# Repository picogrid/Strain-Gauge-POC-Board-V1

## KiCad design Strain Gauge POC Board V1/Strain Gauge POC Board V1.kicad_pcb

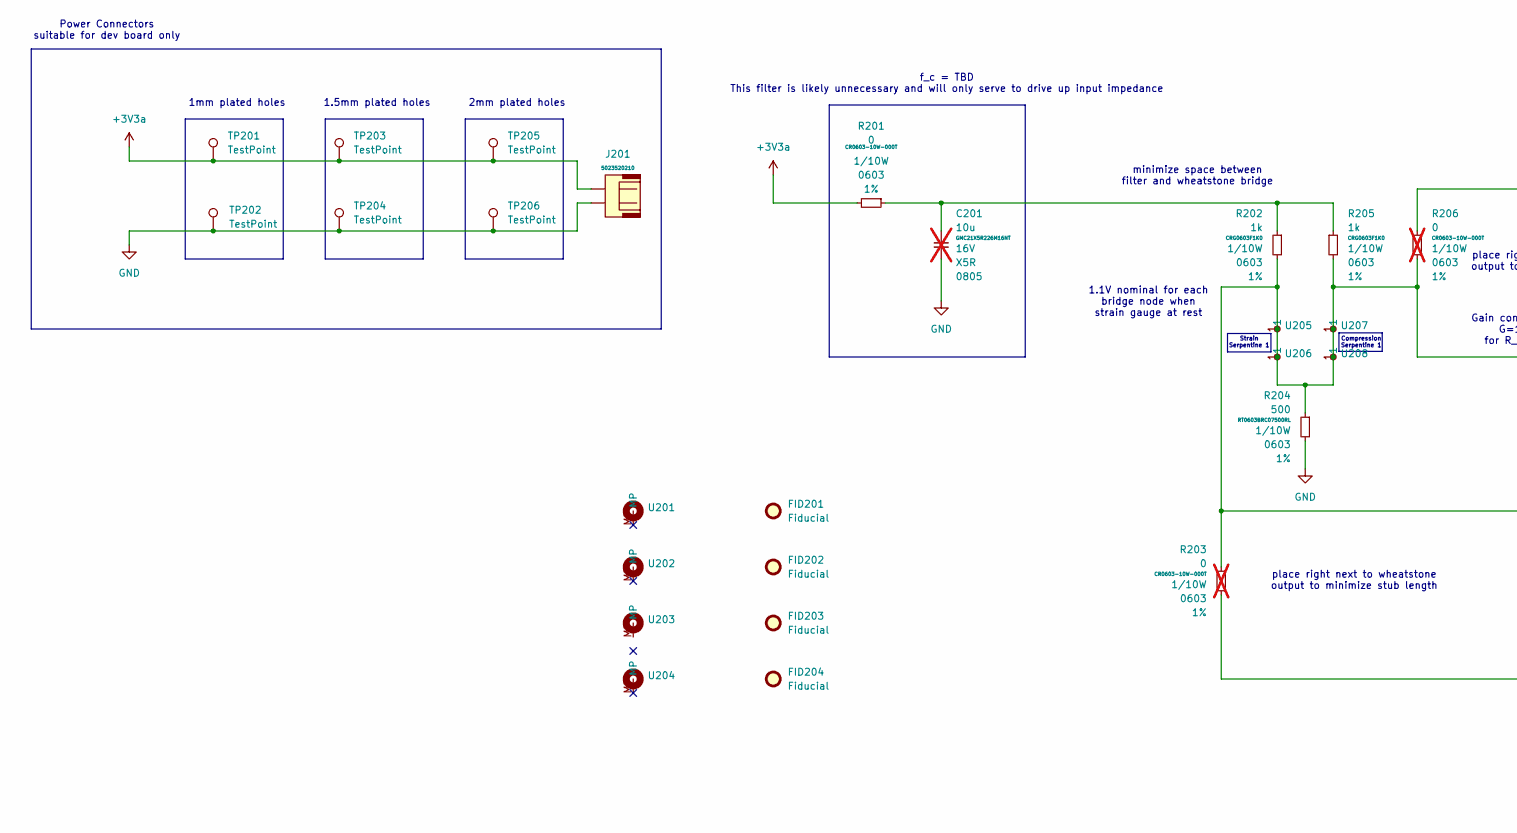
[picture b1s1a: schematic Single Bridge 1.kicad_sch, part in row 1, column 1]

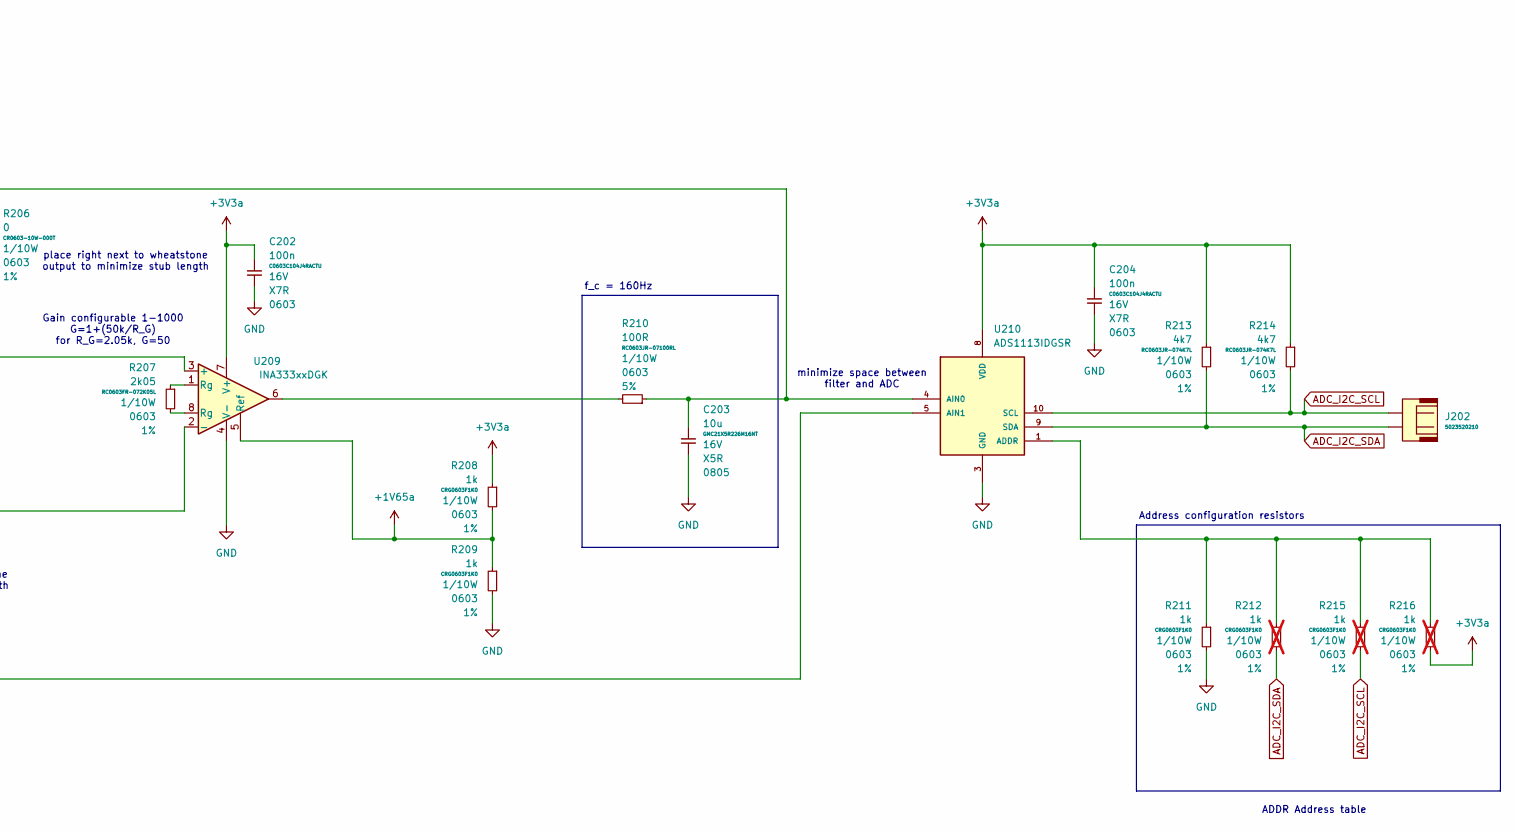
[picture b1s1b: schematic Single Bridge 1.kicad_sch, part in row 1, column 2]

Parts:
C201: 10u; C_0805_2012Metric; Voltage 16V; Mfr PN GMC21X5R226M16NT; not fitted
C202, C204: 100n; C_0603_1608Metric; Voltage 16V; Mfr PN C0603C104J4RACTU
C203: 10u; C_0805_2012Metric; Voltage 16V; Mfr PN GMC21X5R226M16NT
FID201, FID202, FID203, FID204: Fiducial; Fiducial_0.5mm_Mask1mm
J201, J202: 502352-0210; Molex_DuraClik_5023520210_1x02_MP_P2.00mm_Right_Angle; Mfr PN 5023520210
R201: 0; R_0603_1608Metric; Tolerance 1%; Mfr PN CR0603-10W-000T
R202, R205, R208, R209, R211: 1k; R_0603_1608Metric; Tolerance 1%; Mfr PN CRG0603F1K0
R203, R206: 0; R_0603_1608Metric; Tolerance 1%; Mfr PN CR0603-10W-000T; not fitted
R204: 500; R_0603_1608Metric; Tolerance 1%; Mfr PN RT0603BRC07500RL
R207: 2k05; R_0603_1608Metric; Tolerance 1%; Mfr PN RC0603FR-072K05L
R210: 100R; R_0603_1608Metric; Tolerance 5%; Mfr PN RC0603JR-07100RL
R212, R215, R216: 1k; R_0603_1608Metric; Tolerance 1%; Mfr PN CRG0603F1K0; not fitted
R213, R214: 4k7; R_0603_1608Metric; Tolerance 1%; Mfr PN RC0603JR-074K7L
TP201, TP202: TestPoint; TestPoint_THTPad_D2.0mm_Drill1.0mm
TP203, TP204: TestPoint; TestPoint_THTPad_D3.0mm_Drill1.5mm
TP205, TP206: TestPoint; TestPoint_THTPad_D4.0mm_Drill2.0mm
U201, U202, U203, U204: MountingHole_3.2mm_M2_Pad_Via
U205, U206, U207, U208: TestPoint_Pad_D0.15mm
U209: INA333xxDGK; VSSOP-8_3x3mm_P0.65mm
U210: ADS1113IDGSR; SOP50P490X110-10N

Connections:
+1V65a: R208.2, R209.1, U209.5 (Ref)
+3V3a: C202.1 (+), C204.1 (+), J201.1, R201.2, R208.1, R213.1, R214.1, R216.2, TP201.1, TP203.1, TP205.1, U209.7 (V+), U210.8 (VDD)
ADC_I2C_SCL: J202.2, R214.2, R215.2, U210.10 (SCL)
ADC_I2C_SDA: J202.1, R212.2, R213.2, U210.9 (SDA)
GND: C201.2 (-), C202.2 (-), C203.2 (-), C204.2 (-), J201.2, R204.2, R209.2, R211.2, TP202.1, TP204.1, TP206.1, U209.4 (V-), U210.3 (GND)
unnamed: C201.1 (+), R201.1, R202.1, R205.1
unnamed: C203.1 (+), R206.1, R210.1, U210.4 (AIN0)
unnamed: R207.1, U209.1 (Rg)
unnamed: R207.2, U209.8 (Rg)
unnamed: R210.2, U209.6
unnamed: R202.2, R203.1, R204.1, R205.2, R206.2, U205.1, U206.1, U207.1, U208.1, U209.2 (-), U209.3 (+)
unnamed: R211.1, R212.1, R215.1, R216.1, U210.1 (ADDR)
unnamed: R203.2, U210.5 (AIN1)

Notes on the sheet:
Compression Serpentine 1
f_c = 160Hz
Power Connectors suitable for dev board only
Address configuration resistors
1mm plated holes
2mm plated holes
1.1V nominal for each bridge node when strain gauge at rest
Gain configurable 1-1000 G=1+(50k/R_G) for R_G=2.05k, G=50
minimize space between filter and ADC
place right next to wheatstone output to minimize stub length
ADDR Address table
Strain Serpentine 1
1.5mm plated holes
f_c = TBD This filter is likely unnecessary and will only serve to drive up input impedance
minimize space between filter and wheatstone bridge

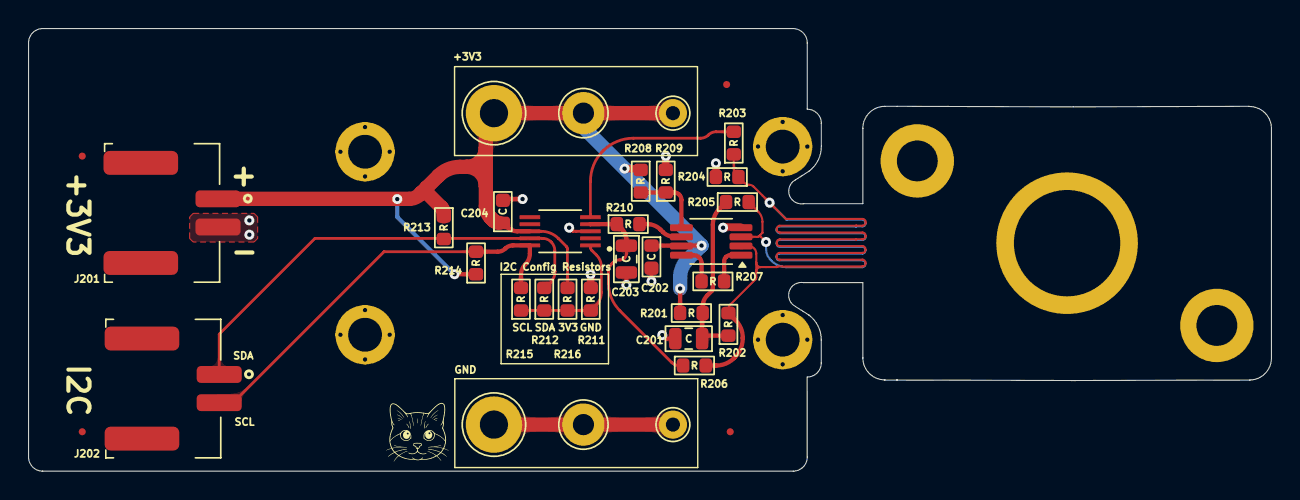
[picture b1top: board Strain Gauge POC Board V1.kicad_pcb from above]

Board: 4 copper layers, 88.2 x 31.4 mm, 42 parts (0 on the bottom side), 13 nets.

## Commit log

2025-06-04 initial git creation from previous work
2025-06-04 Working now
2025-06-04 bulk of first draft done
2025-06-05 further dev
2025-06-05 almost finished first draft
2025-06-05 Ready for fab sans watermark
2025-06-05 final save before duplication
    saved draft in templates
2025-06-05 fixed
2025-06-05 ready for fab
2025-06-05 ready for fab for real this time
2025-06-05 fabbed edition
